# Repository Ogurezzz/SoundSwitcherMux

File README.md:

# SoundSwitcherMux
This switcher uses 74HC4051 to switch between 4 stereo sources to one speaker.

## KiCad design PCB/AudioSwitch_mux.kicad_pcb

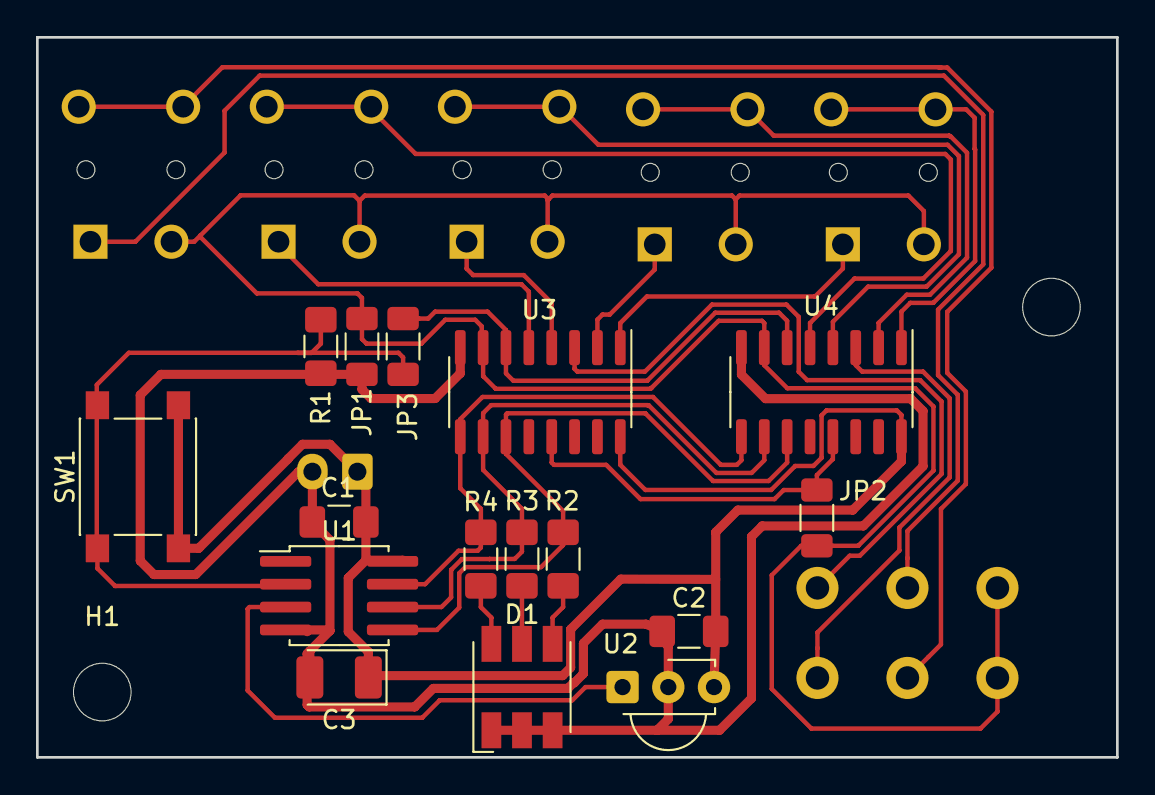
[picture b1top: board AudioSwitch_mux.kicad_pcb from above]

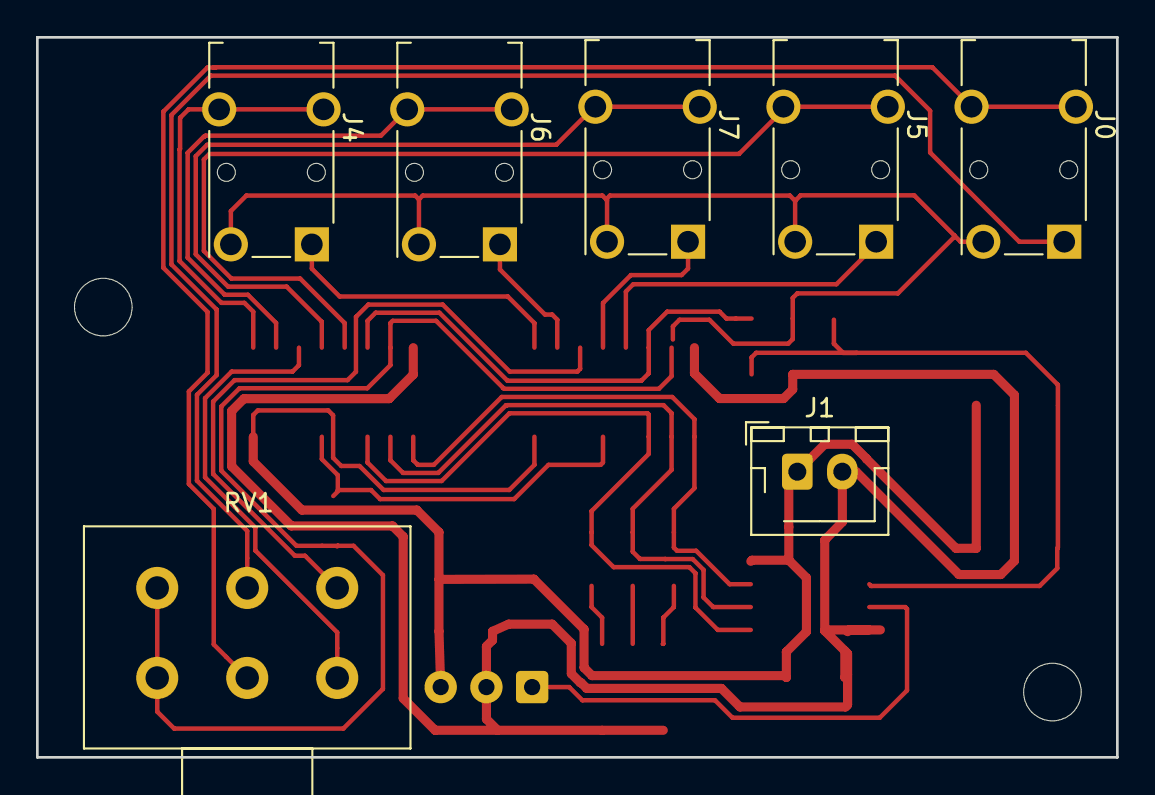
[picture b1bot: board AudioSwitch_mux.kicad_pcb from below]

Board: 2 copper layers, 60.0 x 40.0 mm, 25 parts (7 on the bottom side), 25 nets.

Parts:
C1, C2: 0.1uF; C_1206_3216Metric_Pad1.42x1.75mm_HandSolder
C3: 4.7uF; CP_EIA-3528-21_Kemet-B_Pad1.50x2.35mm_HandSolder
D1: LED_RGB_EP; LED_RGB_5050-6
H1, H2: MountingHole; MountingHole_3.2mm_M3
J0, J4, J5, J6, J7: AudioJack3; Jack_3.5mm_Switronic_ST-005-G_horizontal
J1: Conn_01x02_Male; JST_XH_B2B-XH-AM_1x02_P2.50mm_Vertical
JP1, JP2, JP3: Jumper_2_Open; R_1206_3216Metric_Pad1.30x1.75mm_HandSolder
R1: 10k; R_1206_3216Metric_Pad1.42x1.75mm_HandSolder
R2, R3, R4: 1k; R_1206_3216Metric_Pad1.42x1.75mm_HandSolder
RV1: R_POT_Dual; Potentiometer_Alps_RK163_Dual_Horizontal
SW1: SW_Push; SW_Push_1P1T_NO_6x6mm_H9.5mm
U1: ATtiny25-20SSU; SOIC-8_5.275x5.275mm_P1.27mm
U2: TSMP58138; Vishay_MINICAST-3Pin
U3, U4: 74HC4051; SOIC-16_3.9x9.9mm_P1.27mm

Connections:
GND: C1.2, C2.2, C3.2, D1.1, D1.2, D1.3, J1.2, JP1.2, R1.1, U1.4, U2.2, U3.8, U4.8
unnamed: D1.4, R2.2
unnamed: D1.5, R3.2
unnamed: D1.6, R4.2
unnamed: J0.R, RV1.5
unnamed: J0.S, J4.S, J5.S, J6.S, J7.S, JP1.1, JP2.2, RV1.1, RV1.4, U3.7, U4.7
unnamed: J0.T, RV1.2
unnamed: J4.R, U3.1
unnamed: J4.T, U4.1
unnamed: J5.R, U3.5
unnamed: J5.T, U4.5
unnamed: J6.R, U3.2
unnamed: J6.T, U4.2
unnamed: J7.R, U3.4
unnamed: J7.T, U4.4
unnamed: JP2.1, U3.13, U4.13
unnamed: JP3.1, R1.2, SW1.1, U1.2
unnamed: JP3.2, U3.6, U4.6
unnamed: R2.1, U1.5, U3.11, U4.11
unnamed: R3.1, U1.6, U3.10, U4.10
unnamed: R4.1, U1.7, U3.9, U4.9
unnamed: RV1.3, U4.3
unnamed: RV1.6, U3.3
unnamed: U1.3, U2.1
VCC: C1.1, C2.1, C3.1, J1.1, SW1.2, U1.8, U2.3, U3.16, U4.16

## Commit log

2021-04-18 Added main.c
2021-04-18 Excluded KiCAD *.*-bak files
2021-04-18 Added KiCAD PCB Project
2022-07-19 Update .gitignore, LICENSE, and 5 more files...
